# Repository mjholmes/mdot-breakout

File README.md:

# MDOT breakout
#### A breakout and evaluation board for Multitech MDOT

This is a simple board that breaks out the main connectors from a Multitech MDOT module. It consists of

 - 3 LEDs (DIO3, DIO6, PC13) and a power LED
 - Dallas 1-wire temperature sensor (DIO2)
 - 2 switches (DIO7, PA11) and a reset switch
 - FTDI headers for serial and debug ports
 - JTAG header pins
 
 MDOT developer guide: http://www.multitech.com/manuals/s000612_6.pdf

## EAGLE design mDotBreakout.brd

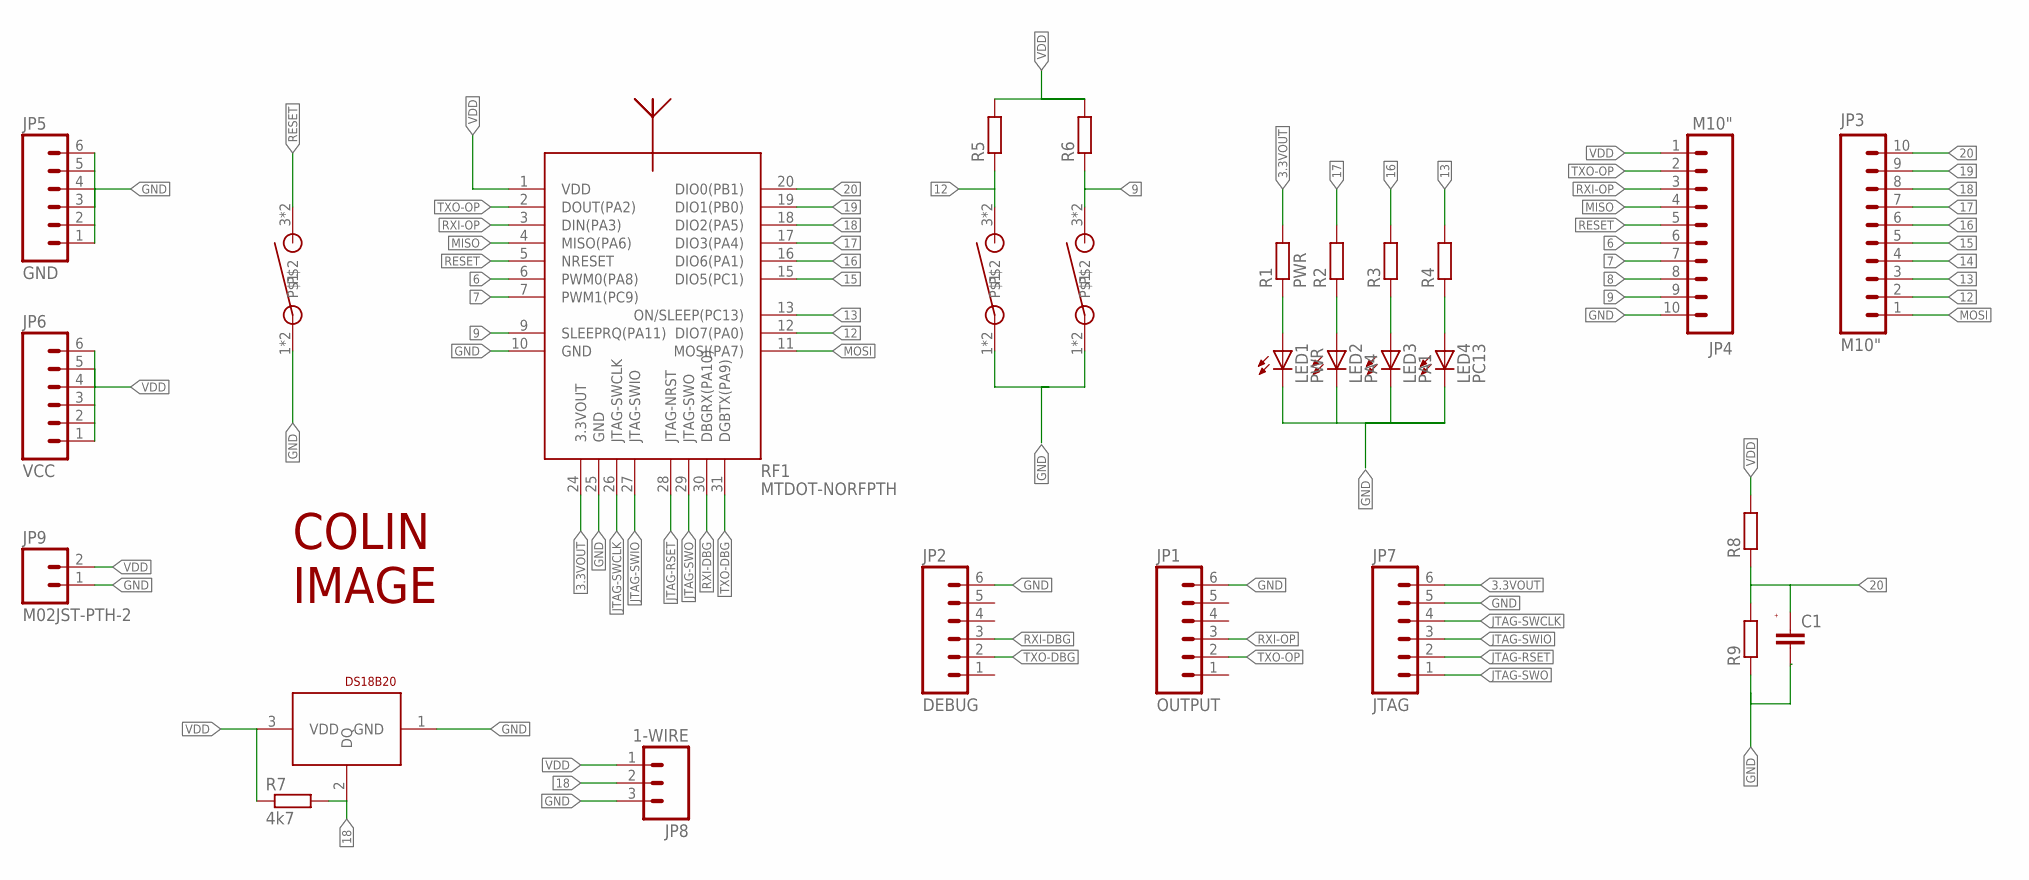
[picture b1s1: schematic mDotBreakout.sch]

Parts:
C1: C-EUC0805K; C0805K
JP1: OUTPUT; 1X06
JP2: DEBUG; 1X06
JP3, JP4: M10"; 1X10
JP5: GND; 1X06
JP6: VCC; 1X06
JP7: JTAG; 1X06
JP8: 1-WIRE; JST-3-PTH
JP9: M02JST-PTH-2; JST-2-PTH
LED1: PWR; CHIPLED_0805
LED2: PA4; CHIPLED_0805
LED3: PA1; CHIPLED_0805
LED4: PC13; CHIPLED_0805
R1: PWR; R0805
R2, R3, R4, R5, R6, R8, R9: R-EUR0805; R0805
R7: 4k7; R0805
RF1: MTDOT-NORFPTH; MTDOT-M1-TRC-PTH-NORF
RST: SWITCH_SPSTPTS645_SMT; PTS645_SMT
U$2, U$3: SWITCH_SPSTPTS645_SMT; PTS645_SMT
U$4: DS18B20TO92; TO92
U$5: COLIN

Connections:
3.3VOUT: JP7.6, R1.2, RF1.24 (3.3VOUT)
6: JP4.6, RF1.6 (PWM0(PA8))
7: JP4.7, RF1.7 (PWM1(PC9))
8: JP4.8
9: JP4.9, R6.1, RF1.9 (SLEEPRQ(PA11)), U$3.3, U$3.4
12: JP3.2, R5.1, RF1.12 (DIO7(PA0)), U$2.3, U$2.4
13: JP3.3, R4.2, RF1.13 (ON/SLEEP(PC13))
14: JP3.4
15: JP3.5, RF1.15 (DIO5(PC1))
16: JP3.6, R3.2, RF1.16 (DIO6(PA1))
17: JP3.7, R2.2, RF1.17 (DIO3(PA4))
18: JP3.8, JP8.2, R7.2, RF1.18 (DIO2(PA5)), U$4.2 (DQ)
19: JP3.9, RF1.19 (DIO1(PB0))
20: C1.1, JP3.10, R8.1, R9.2, RF1.20 (DIO0(PB1))
GND: C1.2, JP1.6, JP2.6, JP4.10, JP5.1, JP5.2, JP5.3, JP5.4, JP5.5, JP5.6, JP7.5, JP8.3, JP9.1, LED1.C, LED2.C, LED3.C, LED4.C, R9.1, RF1.10 (GND), RF1.25 (GND), RST.1, RST.2, U$2.1, U$2.2, U$3.1, U$3.2, U$4.1 (GND)
JTAG-RSET: JP7.2, RF1.28 (JTAG-NRST)
JTAG-SWCLK: JP7.4, RF1.26 (JTAG-SWCLK)
JTAG-SWIO: JP7.3, RF1.27 (JTAG-SWIO)
JTAG-SWO: JP7.1, RF1.29 (JTAG-SWO)
MISO: JP4.4, RF1.4 (MISO(PA6))
MOSI: JP3.1, RF1.11 (MOSI(PA7))
unnamed: LED1.A, R1.1
unnamed: LED2.A, R2.1
unnamed: LED3.A, R3.1
unnamed: LED4.A, R4.1
RESET: JP4.5, RF1.5 (NRESET), RST.3, RST.4
RXI-DBG: JP2.3, RF1.30 (DBGRX(PA10))
RXI-OP: JP1.3, JP4.3, RF1.3 (DIN(PA3))
TXO-DBG: JP2.2, RF1.31 (DGBTX(PA9))
TXO-OP: JP1.2, JP4.2, RF1.2 (DOUT(PA2))
VDD: JP4.1, JP6.1, JP6.2, JP6.3, JP6.4, JP6.5, JP6.6, JP8.1, JP9.2, R5.2, R6.2, R7.1, R8.2, RF1.1 (VDD), U$4.3 (VDD)

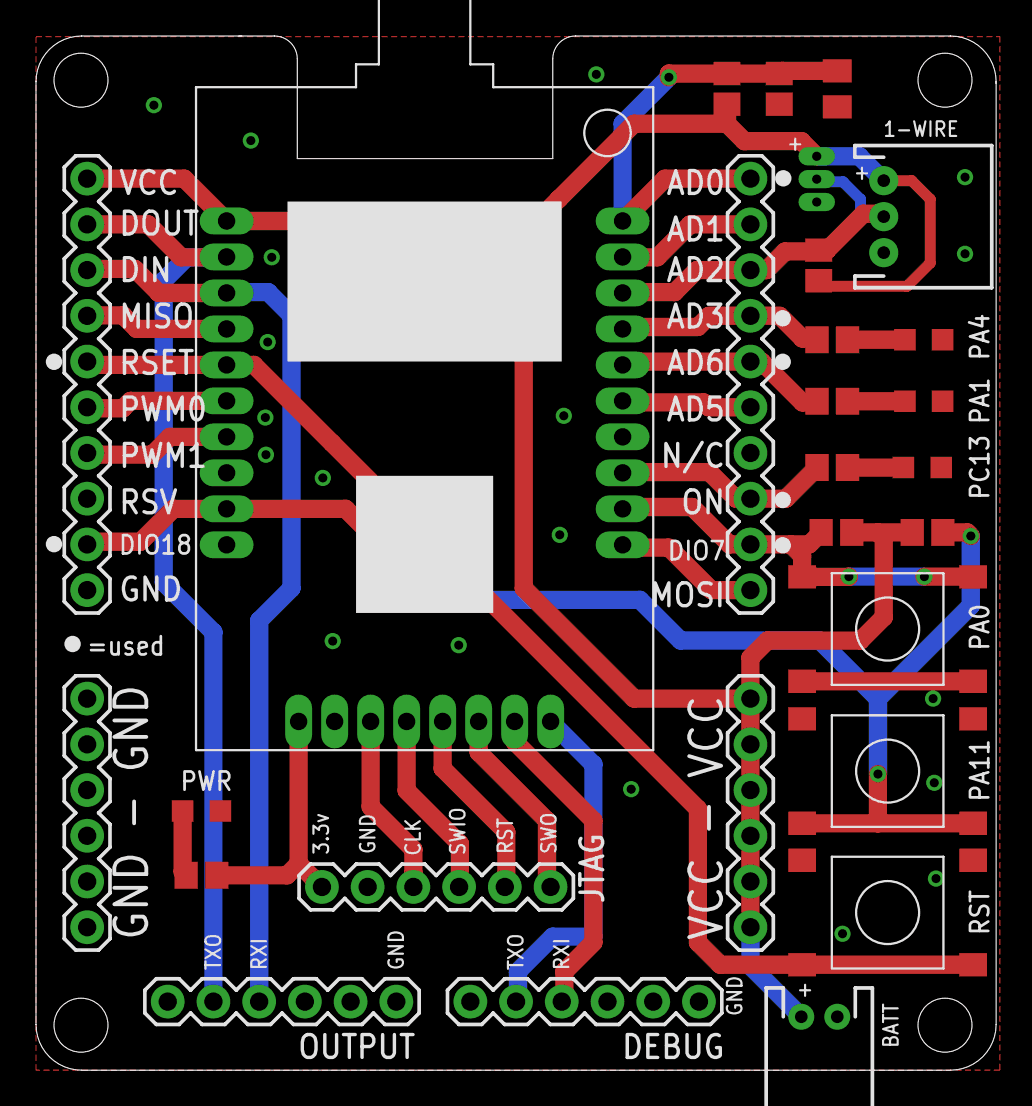
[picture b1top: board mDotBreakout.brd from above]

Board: 2 copper layers, 53.3 x 57.5 mm, 29 parts (1 on the bottom side), 29 nets.

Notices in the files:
parts and their libraries:
SparkFun-Connectors: Licensing: CC v3.0 Share-Alike You are welcome to use this library for commercial purposes.
